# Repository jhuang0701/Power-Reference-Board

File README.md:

# 3-Phase FOC BLDC Motor Driver with Onboard IMU

A custom 4-layer PCB for field-oriented control (FOC) of a brushless DC motor, with an onboard IMU for real-time orientation feedback. Designed in KiCad, targeting a self-balancing single-wheel robot or reaction-wheel inverted pendulum as the demo application.

This is a design-only project: schematic and layout are complete and DRC-clean. Fabrication is a separate decision, not yet made.

## What it does

The board takes a 6S battery input (22.2V nominal, up to 25.2V) and drives a 3-phase BLDC motor using field-oriented control, with current feedback and IMU data available for a real-time stabilization loop. It's built around three main subsystems: power delivery and protection, the 3-phase gate drive and half-bridge power stage, and the sensing/control electronics.

## Core components

- **MCU:** STM32G474RET6 (LQFP-64). Chosen specifically for its onboard op-amps, which are used directly for current-sense amplification, and for TIM1's hardware dead-time generation on complementary PWM channels.
- **Gate driver:** DRV8353HRTAT, a 102V-rated 3-phase smart gate driver in hardware-interface mode (no SPI on this variant), configured via resistor-divider pins for 6x independent PWM mode.
- **Phase MOSFETs:** 6x CSD18540Q5BT (60V, 2.2mΩ RDS(on)), two per phase leg.
- **IMU:** ICM-42688-P, 6-axis accelerometer/gyroscope, connected over SPI.
- **Buck converter:** TPS54331DR, steps the battery rail down to a clean 3.3V supply for the MCU and IMU.
- **Reverse-polarity protection:** a 7th CSD18540Q5BT, wired low-side in the ground return path, with a Zener-clamped gate bias network. (An earlier design used a small P-channel MOSFET for this; it was replaced after checking its actual gate-voltage rating against the battery voltage and finding it wouldn't survive.)

## Design decisions worth knowing about

**Dual current-sensing paths.** The DRV8353HRTAT's built-in shunt amplifiers are used only for the driver's own hardware overcurrent protection, independent of the MCU. The actual current feedback used for the FOC control loop comes from the STM32G474's internal op-amps, wired directly to the same shunt resistors. Two separate paths, one fast and hardware-only for protection, one precise and MCU-driven for control.

**Hardware dead-time via TIM1.** Rather than relying on the gate driver's default switching behavior, all six gate signals (INHx/INLx) are driven independently from the MCU's TIM1 timer, which generates dead-time insertion in hardware. This gives direct control over switching behavior rather than trusting a fixed driver-side default.

**Mixed-signal supply isolation.** VDDA (the MCU's analog supply, feeding the ADC and current-sense op-amps) is isolated from the main 3.3V digital rail with a series resistor and its own local decoupling, keeping switching noise out of the current measurements.

## Specs

| | |
|---|---|
| Input | 6S Li-ion, 22.2V nominal / 25.2V max |
| Phase current | 15A continuous, 30A peak |
| Board | 4-layer, 60x60mm, 2oz outer copper |
| MCU | STM32G474RET6 |
| Gate driver | DRV8353HRTAT |
| IMU | ICM-42688-P (SPI) |

## Repo contents

- `/schematic` - full schematic PDF export
- `/gerbers` - fabrication-ready Gerber files
- `/bom` - bill of materials
- `/renders` - 3D board renders and layout screenshots

## Status

Schematic and layout complete, DRC-clean. Fabrication not yet started.

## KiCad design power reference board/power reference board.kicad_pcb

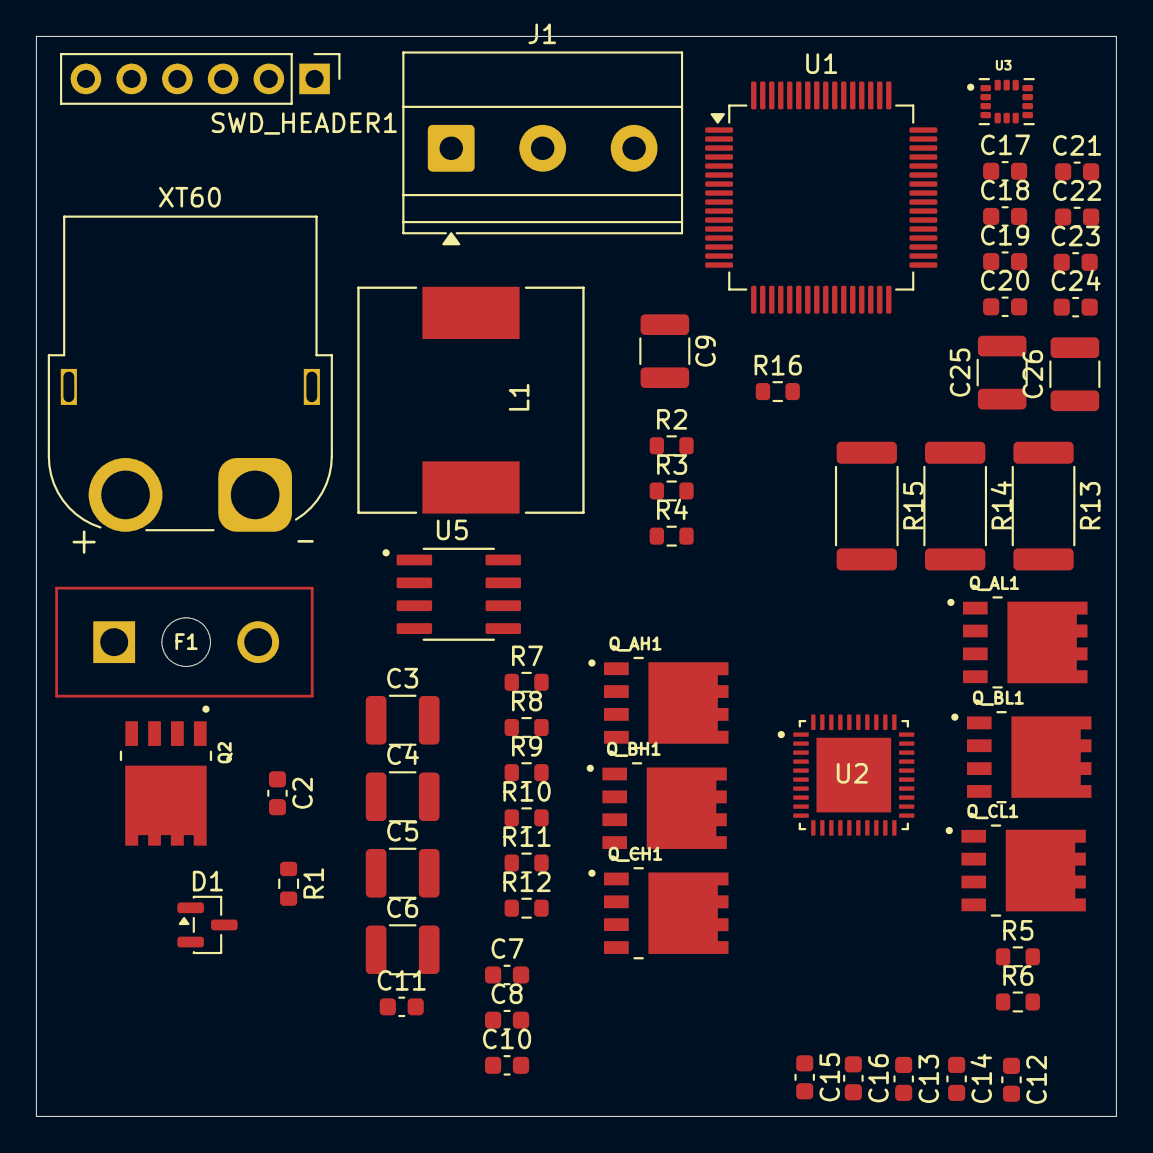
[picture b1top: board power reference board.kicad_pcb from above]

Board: 4 copper layers, 60.0 x 60.0 mm, 58 parts (0 on the bottom side), 56 nets, no tracks yet.

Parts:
C2: 1000µF/35V; C_0603_1608Metric
C3, C4, C5, C6: 10µF; C_1210_3225Metric
C7, C11, C16: 0.1µF; C_0603_1608Metric
C8, C10: 10nF; C_0603_1608Metric
C9: 22µF; C_1210_3225Metric
C12, C13, C15, C21, C23: 1µF; C_0603_1608Metric
C14: 47nF; C_0603_1608Metric
C17, C18, C19, C20, C22, C24: 100nF; C_0603_1608Metric
C25, C26: 100nF; C_1210_3225Metric
D1: BZX84Cxx; SOT-23
F1: 178.6764.0001; LITTLEFUSE_178.6764.0001
J1: Conn_01x03; TerminalBlock_Phoenix_MKDS-1,5-3-5.08_1x03_P5.08mm_Horizont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
L1: SRR1260-220M; INDP125125X600N
Q2: CSD18540Q5BT; TRANS_CSD18540Q5BT
Q_AH1: CSD18540Q5BT; TRANS_CSD18540Q5BT
Q_AL1: CSD18540Q5BT; TRANS_CSD18540Q5BT
Q_BH1: CSD18540Q5BT; TRANS_CSD18540Q5BT
Q_BL1: CSD18540Q5BT; TRANS_CSD18540Q5BT
Q_CH1: CSD18540Q5BT; TRANS_CSD18540Q5BT
Q_CL1: CSD18540Q5BT; TRANS_CSD18540Q5BT
R1, R2, R4, R6: 10kΩ; R_0603_1608Metric
R3: 3.24kΩ; R_0603_1608Metric
R5: 100Ω; R_0603_1608Metric
R7, R8, R9, R10, R11, R12, R16: 10Ω; R_0603_1608Metric
R13, R14, R15: 2mΩ; R_2512_6332Metric
SWD_HEADER1: Conn_01x06; PinHeader_1x06_P2.54mm_Vertical
U1: STM32G474RETx; LQFP-64_10x10mm_P0.5mm
U2: DRV8353HRTAT; QFN50P600X600X80-41N
U3: ICM-42688-P; PQFN50P300X250X97-14N
U5: TPS54331DR; SOIC127P599X175-8N
XT60: Conn_01x02; AMASS_XT60PW-F_1x02_P7.20mm_Horizontal

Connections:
+3.3V: C17.2, C18.2, C19.2, C20.2, C25.2, C26.2, R16.2, SWD_HEADER1.1, U1.1 (VBAT), U1.16 (VDD), U1.32 (VDD), U1.48 (VDD), U1.64 (VDD), U3.5 (VDDIO), U3.8 (VDD)
FB: R2.1, R3.2, U5.5 (VSENSE)
GATE_PROT: D1.3 (K), Q2.4, R1.2
GND: C2.2, C3.1, C4.1, C5.1, C6.1, C8.2, C9.1, C10.1, C11.1, C13.2, C15.2, C16.2, C17.1, C18.1, C19.1, C20.1, C21.1, C22.1, C23.1, C24.1, C25.1, C26.1, D1.1 (A), Q2.5_6_7_8, R3.1, R13.1, R14.1, R15.1, SWD_HEADER1.4, U1.15 (VSS), U1.19 (PA5), U1.23 (PC5), U1.26 (PB2), U1.27 (VSSA), U1.31 (VSS), U1.47 (VSS), U1.63 (VSS), U2.10 (SNA), U2.11 (SNB), U2.20 (SNC), U2.25 (AGND), U2.27 (MODE), U2.39 (GND), U2.41 (EXP), U3.6 (GND), U5.7 (GND)
GND_RAW: Q2.1, Q2.2, Q2.3, XT60.2
unnamed: C9.2, L1.1, R2.2
unnamed: C10.2, R4.1
unnamed: Q_AH1.4, R7.1
unnamed: Q_AL1.4, R8.1
unnamed: Q_BH1.4, R9.1
unnamed: Q_BL1.4, R10.1
unnamed: Q_CH1.4, R11.1
unnamed: Q_CL1.4, R12.1
unnamed: SWD_HEADER1.2, U1.49 (PA13)
unnamed: SWD_HEADER1.3, U1.50 (PA14)
unnamed: SWD_HEADER1.5, U1.56 (PB3)
unnamed: SWD_HEADER1.6, U1.7 (PG10)
unnamed: U1.21 (PA7), U2.33 (INLA)
unnamed: U1.42 (PA8), U2.32 (INHA)
unnamed: U1.43 (PA9), U2.34 (INHB)
unnamed: U1.44 (PA10), U2.36 (INHC)
unnamed: U1.45 (PA11), U3.4 (INT1/INT)
unnamed: U1.51 (PA15), U3.12 (AP_CS)
unnamed: U1.24 (PB0), U2.35 (INLB)
unnamed: U1.25 (PB1), U2.37 (INLC)
unnamed: R6.1, U1.8 (PC0), U2.26 (~FAULT)
unnamed: U1.52 (PC10), U3.13 (AP_SCL/AP_SCLK)
unnamed: U1.53 (PC11), U3.1 (AP_SDO/AP_AD0)
unnamed: U1.54 (PC12), U3.14 (AP_SDA/AP_SDIO/AP_SDI)
unnamed: U1.2 (PC13), U2.31 (ENABLE)
unnamed: C21.2, C22.2, C23.2, C24.2, R16.1, U1.28 (VREF+), U1.29 (VDDA)
unnamed: C14.1, U2.2 (CPH)
unnamed: C14.2, U2.1 (CPL)
unnamed: C15.1, R6.2, U2.38 (DVDD)
unnamed: R7.2, U2.6 (GHA)
unnamed: R9.2, U2.15 (GHB)
unnamed: R11.2, U2.16 (GHC)
unnamed: R8.2, U2.8 (GLA)
unnamed: R10.2, U2.13 (GLB)
unnamed: R12.2, U2.18 (GLC)
unnamed: C12.1, U2.5 (VCP)
unnamed: R5.1, U2.4 (VDRAIN)
unnamed: C13.1, U2.40 (VGLS)
unnamed: C16.1, U2.24 (VREF)
unnamed: C7.1, U5.1 (BOOT)
unnamed: R4.2, U5.6 (COMP)
unnamed: C7.2, L1.2, U5.8 (PH)
unnamed: C8.1, U5.4 (SS)
PHASE_A: J1.3, Q_AH1.5_6_7_8, Q_AL1.1, Q_AL1.2, Q_AL1.3, U2.7 (SHA)
PHASE_A_SNS: Q_AL1.5_6_7_8, R13.2, U1.17 (PA3), U1.35 (PB13), U2.9 (SPA)
PHASE_B: J1.2, Q_BH1.5_6_7_8, Q_BL1.1, Q_BL1.2, Q_BL1.3, U2.14 (SHB)
PHASE_B_SNS: Q_BL1.5_6_7_8, R14.2, U1.36 (PB14), U2.12 (SPB)
PHASE_C: J1.1, Q_CH1.5_6_7_8, Q_CL1.1, Q_CL1.2, Q_CL1.3, U2.17 (SHC)
PHASE_C_SNS: Q_CL1.5_6_7_8, R15.2, U2.19 (SPC)
VBAT_RAW: F1.P$2, R1.1, XT60.1
VM: C2.1, C3.2, C4.2, C5.2, C6.2, C11.2, C12.2, F1.P$1, Q_AH1.1, Q_AH1.2, Q_AH1.3, Q_BH1.1, Q_BH1.2, Q_BH1.3, Q_CH1.1, Q_CH1.2, Q_CH1.3, R5.2, U2.3 (VM), U5.2 (VIN), U5.3 (EN)
